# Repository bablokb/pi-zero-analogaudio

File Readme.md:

Pi-Zero-Analogaudio
===================

The Pi-Zero is a stripped down board, there is no analog audio jack
like on the bigger Pis. But it is no problem to add it using a few
simple and cheap components.

The schematic

shows the necessary parts and the wiring. Basically, you configure the
Zero to output pwm-signals, then you use a combination of a lowpass
and highpass filter to clean the signal on every channel.

The audio quality is ok, but not on hifi level. The filters limit the
frequency range and the signal is still not absolutely clean afterwards.
If you really need high-quality audio-output, use HDMI, bluetooth or
attach an audio-hat based on I2S using a DAC.

Hardware
========

Required parts:

  - two resistors 270 Ohm
  - two resistors 150 Ohm
  - two capacitors 33nF
  - two capacitors 10µF
  - an 3.5mm audio-jack (e.g. STX-3120-5B from Adafruit)
  - some jumper-wires

In the folder `kicad` you can find a complete pcb, designed for the above
throughhole components. You will need to adapt the design if you use a
different audio-jack.

Software and System Configuration
=================================

You don't need special software, just use `aplay` to play wav-files or
e.g. `mpg123` for mp3-files.

You can configure the system manually, or you can clone the repository
and just run the install command:

    git clone https://github.com/bablokb/pi-zero-analogaudio.git
    cd pi-zero-analogaudio
    sudo tools/install

The install command will add the following lines to your `/boot/config.txt`:

    dtparam=audio=on
    dtoverlay=pwm-2chan,pin=12,func=4,pin2=13,func2=4

This configures analog-audio for the physical pins 32 and 33. Other
pin-combinations are possible, see the file `/boot/overlays/README` for
a complete list.

In addition, the install command runs

    amixer cset numid=3 1

This switches the audio-output from auto (0) or HDMI (2) to analog-out (1).
You can also use `raspi-config` for this task (or for switching back).

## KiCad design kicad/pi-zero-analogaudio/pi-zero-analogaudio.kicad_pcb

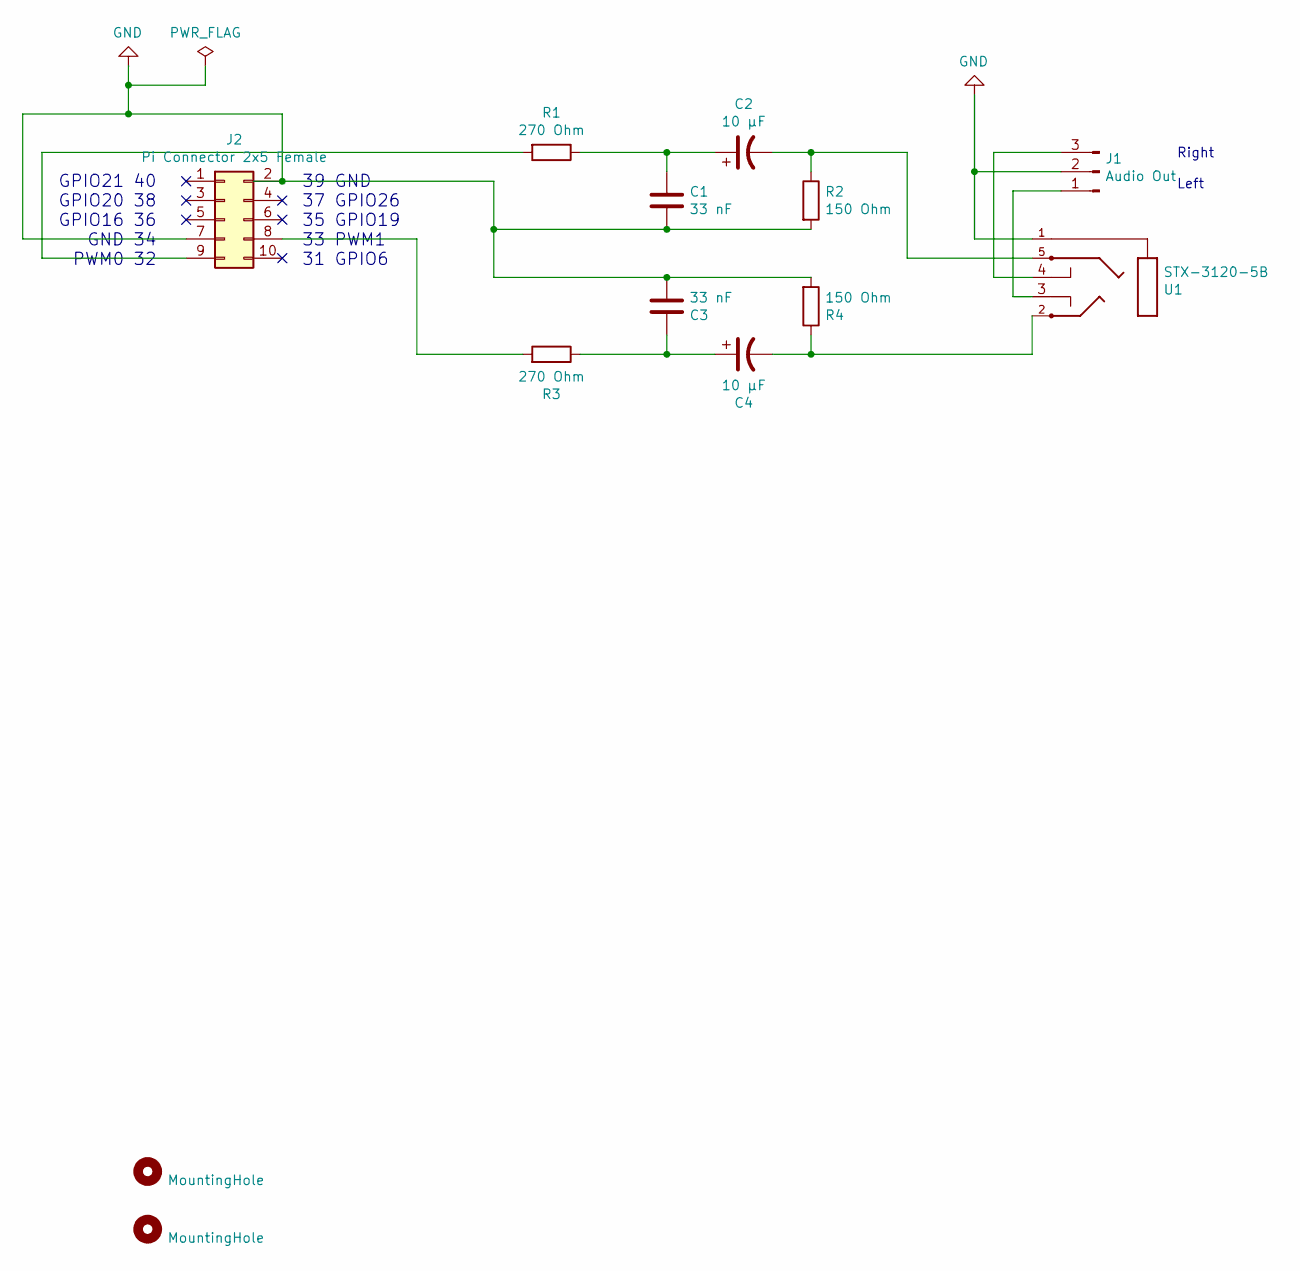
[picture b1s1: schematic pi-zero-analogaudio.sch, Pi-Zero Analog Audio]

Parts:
C1, C3: 33 nF; C_Disc_D3.0mm_W1.6mm_P2.50mm
C2, C4: 10 µF; CP_Radial_D4.0mm_P1.50mm
H1, H2: MountingHole; MountingHole_2.7mm_M2.5_DIN965_Pad
J1: Audio Out; PinHeader_1x03_P2.54mm_Vertical
J2: Pi Connector 2x5 Female; PinSocket_2x05_P2.54mm_Vertical
R1, R3: 270 Ohm; R_Axial_DIN0207_L6.3mm_D2.5mm_P7.62mm_Horizontal
R2, R4: 150 Ohm; R_Axial_DIN0207_L6.3mm_D2.5mm_P7.62mm_Horizontal
U1: STX-3120-5B

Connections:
GND: C1.2, C3.2, J1.2, J2.2, J2.7, R2.2, R4.2, U1.1
unnamed: C1.1, C2.1, R1.1
unnamed: C2.2, R2.1, U1.5
unnamed: C3.1, C4.1, R3.1
unnamed: C4.2, R4.1, U1.2
unnamed: J1.1, U1.3 (L_out)
unnamed: J1.3, U1.4 (R_out)
unnamed: J2.8, R3.2
unnamed: J2.9, R1.2

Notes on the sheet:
GPIO21 40 GPIO20 38 GPIO16 36 GND 34 PWM0 32
Right Left
39 GND 37 GPIO26 35 GPIO19 33 PWM1 31 GPIO6

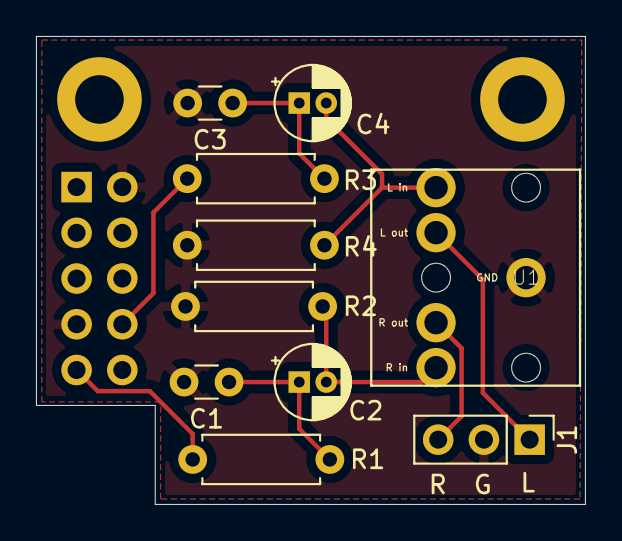
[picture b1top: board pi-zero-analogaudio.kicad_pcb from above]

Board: 2 copper layers, 30.5 x 26.0 mm, 13 parts (1 on the bottom side), 9 nets.

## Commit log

2019-12-23 added 2x5 connector
2019-12-24 changed administrative metadata
2019-12-27 Revision 3: added connector for audio-out
2019-12-28 added footprints and started pcb
2019-12-29 fixed wrong connection for R4
2020-01-04 Revision 5: J3 with additional GND, connect pin34 with pin39
2020-01-04 updated pcb for revision 5
2020-01-04 updated to revision 5
2020-01-07 added GND/PWR_FLAG
2020-01-07 Revision 6: replace generic audio-jack with STX-3120-3B
2020-01-07 updated layout (size, components)
2020-01-08 slightly moved header to (hopefully) fit hat-dimensions
2020-01-08 drilling holes, silk-screen print
2020-01-09 added copper-fill to F.Cu
2020-01-09 Revision 7: mounting-hole with pad / small tweaks
2020-01-09 set labels H1/H2 to invisible
2020-01-12 Revision 8: replaced STX3120-3B with STX3120-5B
2020-01-18 updated to current version
2020-01-18 added cutoff
2020-01-21 optimzed placement of labels
2020-02-06 linked images of pcb
2020-02-07 fix: add dtparam=audio=on to /boot/config.txt
